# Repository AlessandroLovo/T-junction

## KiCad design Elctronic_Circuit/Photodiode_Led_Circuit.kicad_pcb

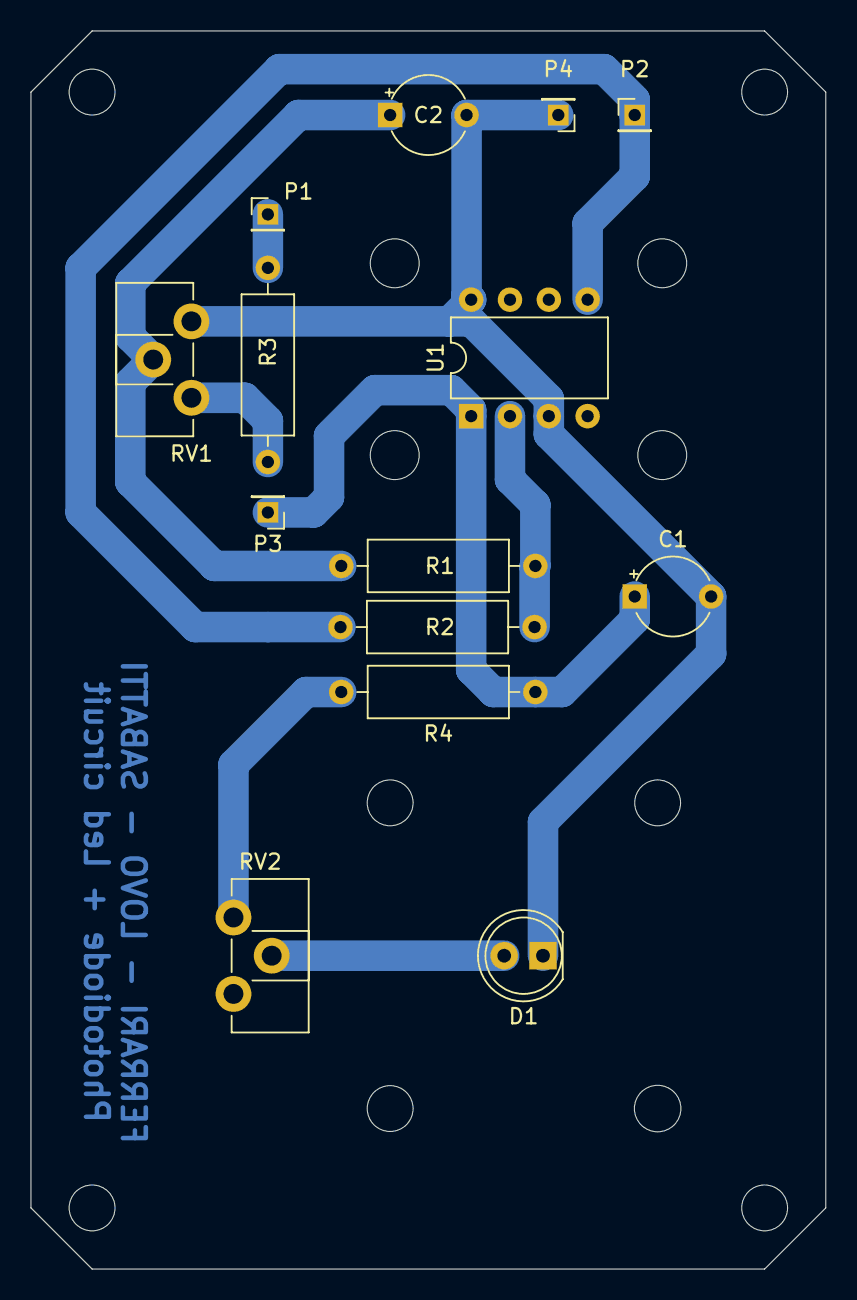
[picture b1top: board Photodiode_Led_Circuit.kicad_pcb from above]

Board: 2 copper layers, 52.0 x 81.0 mm, 14 parts (0 on the bottom side), 9 nets.

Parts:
C1, C2: C; CP_Radial_Tantal_D5.0mm_P5.00mm
D1: LED; LED_D5.0mm
P1: Input; PinHeader_1x01_P2.00mm_Vertical
P2: Output; PinHeader_1x01_P2.00mm_Vertical
P3: Vcc; PinHeader_1x01_P2.00mm_Vertical
P4: GND; PinHeader_1x01_P2.00mm_Vertical
R1, R3, R4: R; R_Axial_DIN0309_L9.0mm_D3.2mm_P12.70mm_Horizontal
R2: 50M; R_Axial_DIN0309_L9.0mm_D3.2mm_P12.70mm_Horizontal
RV1, RV2: POT; Potentiometer_ACP_CA9-H2,5_Horizontal
U1: OPT101; DIP-8_W7.62mm

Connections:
unnamed: C1.1, P3.1, R4.1, U1.1
unnamed: C1.2, C2.2, D1.1, P4.1, RV1.3, U1.3, U1.8
unnamed: C2.1, R1.2, RV1.2
unnamed: D1.2, RV2.2
unnamed: P1.1, R3.1
unnamed: P2.1, R2.1, U1.5
unnamed: R1.1, R2.2, U1.2
unnamed: R3.2, RV1.1
unnamed: R4.2, RV2.1

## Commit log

2020-11-12 now on git
2020-11-13 ideas for data analysis and testing
2020-11-14 aggiunto soglie in testing
2020-11-14 Update soglie
2020-11-18 big progress in image processing
2020-11-18 today data
2020-11-18 image analysis
2020-11-18 trying fft
2020-11-19 added calibration
2020-11-19 19-11 data
2020-11-19 soglie modified
2020-11-19 more image analysis
2020-11-20 image processing almost done
2020-11-20 starting to tidy up
2020-11-21 more tidying up in image processing, perfected mean subtraction to avoid overflow
2020-11-22 image processing ready to be used
2020-11-23 Dropsinator_Rev.1
2020-11-23 Estimating the velocity ideas
2020-11-23 Dropsinator_Rev.1.2
2020-11-24 Dropsinator Rev 1.3 Fourier
2020-11-24 Some tuning on the fft
2020-11-25 Dropsinator_Rev.1.3 modfied
2020-11-25 Dropsinator_Rev.1.4
2020-11-25 minor changes
2020-11-25 Dropsinator_Rev.1.4 fixed start_drop and drop_end
2020-11-25 image processing velocity
2020-11-25 Dropsinator_Rev.1.4 purged
2020-11-25 Dropsinator_Rev.1.4 and images_procesings purged
2020-11-26 image_processing: threshold computing parameters
2020-11-27 Some polishing of the functions and drop_detection_tools.py
2020-11-27 updated jupyter notebok
2020-11-28 aggiunto fit spettro velocità image_processing
2020-11-28 following the droplets along the video
2020-11-28 we can follow droplets!!
2020-11-28 some code polishing
2020-11-29 meeting work on image analysis
2020-12-03 upload data 2-12
2020-12-03 removed .csv.csv, extracted frames from 2-12/B-ol2-aq2-spf1
2020-12-04 Dropsinator_Rev2 added
2020-12-04 flipped y axis
2020-12-04 Dropsinator_Rev2.1
2020-12-04 some work on the images: the videos really suck!
2020-12-04 aggiunta cartella Report
2020-12-05 dropsinator_rev2.1 sistemated
2020-12-05 Dropsinator_Rev1.2 added
2020-12-05 Dropsinator_Rev2.3
2020-12-05 Dropsinator 2.3 advancements: now latex plots work
2020-12-05 dropsinator 2.2
2020-12-06 small change dropsinator2.3
2020-12-07 maybe issue in image analysis
2020-12-07 Issue was in the file names: solved!
2020-12-07 Some image analysis and correlation plots
2020-12-07 kernel keeps dying
2020-12-08 some cool stuff on image analysis: batching and signal normalization
2020-12-08 some more plots
2020-12-08 style fixes to correlation plot
2020-12-09 enabled deactivated freqs on FFT_cropping
2020-12-09 aggiunto verbale 20201209
2020-12-09 discovered issue with time
2020-12-09 ddt.resample
2020-12-09 normalize signal for efficient delay computing
2020-12-09 Dropsinator Rev. 2.4
2020-12-10 Add function for drop slopes
2020-12-10 Riordinamento cartelle
2020-12-10 Aggiunto circuito KiCad
2020-12-10 Riordimaneto cartelle
2020-12-10 Dropsinator_Rev2.4
2020-12-10 fixed plot saving in Dropsinator_Rev2.4 and image_processing_Rev1
2020-12-11 meeting 11-12
2020-12-11 macro raddrizzamento
2020-12-11 signal rectification
2020-12-11 some work on report
2020-12-11 wide_start, wide_end
2020-12-11 Rectifier_Rev1
2020-12-12 add wide_narrow_drops
2020-12-12 slopes function
2020-12-12 fixed latex plots
2020-12-12 add wide_narrow_drops Rev1.2
2020-12-12 tried raytracing... too complicated
2020-12-12 image processing for relation
2020-12-13 some more relation
2020-12-13 Signal_Rectifier_Rev1.1, Dropsinator_Rev2.5 e mod. libreria ddt
2020-12-15 some modifications to Wide-narrow drops
2020-12-15 Signal_Rectifier_Rev1.2 e mod. libreria ddt
2020-12-15 huge progress !!!
2020-12-16 meeting work
2020-12-16 Signal_Rectifier_Rev1.3 e mod. libreria ddt
2020-12-16 Dropsinator_Rev2.6
2020-12-17 added return sigma 1 2 in ddr.thr_searcher
2020-12-17 ddt.rectify_new docstring and more versatile plots
2020-12-17 I missed a few things
2020-12-17 add dropsinator 3.1
2020-12-17 drop_det_new doesn't work very well on images
2020-12-17 modified dropsinator 3.1
2020-12-17 fixed ddt.drop_det_new for images
2020-12-17 ufloats
2020-12-17 dropsin 3.1 modified
2020-12-17 starting the uplotlib
2020-12-17 uplotlib
2020-12-18 first uplot
2020-12-18 uplot small modify
2020-12-18 slope function copied in ddt library
2020-12-18 shaving some functions in ddt
2020-12-18 important bug fix to ddt.drop_det_new
2020-12-18 another bug fix to ddt.drop_det_new
2020-12-18 dropsin 3.1 almost finished
2020-12-18 proceding with image analysis
2020-12-18 progress on image analyisis
2020-12-18 dropsinator 3.1 finished
2020-12-18 one plot
2020-12-19 continuing with ia
2020-12-19 Dropsinator_Fail
2020-12-19 resetting Dropsinator3.1
2020-12-19 first results in ia
2020-12-19 Dropsinator test
2020-12-20 simplifying name handling and removing useless lines in Dropsinator
2020-12-20 more work on ia
2020-12-20 more ia
2020-12-20 ol2aq2 and ol3aq7 analisys
2020-12-20 ia is done!!!
2020-12-20 minor tweaks
2020-12-20 adding units to saved fit parameters
2020-12-20 meeting work on Dropsinator
2020-12-20 dropsin3.1 modify parameters file and add menisque
2020-12-21 Dropsinator scrauso
2020-12-21 ray tracing
2020-12-21 figure d'aiuto per la comprensione della forma d'onda
2020-12-22 articles for report
2020-12-22 articles for report (2 more)
2020-12-22 more raytracing
2020-12-22 nothing special
2020-12-23 meeting
2020-12-23 meeting 23-12
2020-12-24 WE HAVE THE SHOULDER
2020-12-26 A lot of ray tracing
2020-12-26 All frame extraction and calibration of 2-12 ia
2020-12-26 a little more raytracing
2020-12-27 added possibility to manually change drop edges in Dropsinator
2020-12-27 first full simulated waveform
2020-12-28 some small adjustments
2020-12-28 meeting showage
2020-12-30 dropsinator plot fix
2020-12-30 standardized saving fit results
2020-12-30 some image analysis
2020-12-30 relation work
2020-12-30 Sono stanco :)
2020-12-31 2-2,5-5,3-7 analisi elettronica
2020-12-31 2-2,5-5,3-7 analisi elettronica, un re-plot
2020-12-31 3-7 modified
2020-12-31 3-7 double fit for distance
2020-12-31 uplt.df2latex
2020-12-31 added the second part of the results for the double fit that was missing in 2-12_B-ol3-aq7_e.csv
2020-12-31 Ray tracing per relazione
2020-12-31 meeting 31-12
2020-12-31 15-5 analisi
2020-12-31 10-10 ci abbiamo capito qualcosa
2020-12-31 ddt.drop_det_new should work much better now
2021-01-01 ia_1.3
2021-01-01 report work
2021-01-01 redoing some ia
2021-01-01 10-10 analisi
2021-01-01 30-10 analisi
2021-01-03 Ray_tracying_1.3b
2021-01-10 finished ia on 2-12/B*, started analyzing also 2-12/A* but chip A is tricky
2021-01-14 meeting 14-01
2021-01-16 first electronic chip A analysis
2021-01-22 almost finished the analysis of 2-12/A*. A-10-10 is particularly difficult to analyze: up to now it needs to be analyzed again
2021-02-19 Two new documents from Giovanni Bragato
2021-02-19 Finisher_Rev0 per l'analisi dei dataframe
2021-02-20 Finisher_Rev0 aggiornamento
2021-02-24 2-2 and 5-5 redo for missing parameters
2021-02-25 circularity of the capillary plot saved
2021-02-26 Finisher_Rev1 aggiornamento
2021-02-26 modifiche per scrivere relazione - 10-10 corretto
2021-02-26 Finisher_Rev1: ratio distance/size fixed
2021-02-27 Artificial data misalignment for visualization purposes
2021-02-27 meeting work on Finisher
2021-02-28 Finisher_Rev2
2021-02-28 study on why we need resampling
2021-03-02 we underestimate the velocity in the electronic analysis
2021-03-02 meeting work, nothing remarkable
2021-03-04 internal photodiode circuit figure
2021-03-04 figure
2021-03-05 circularity cropped
2021-03-05 added final report to git
2021-04-01 presentation
